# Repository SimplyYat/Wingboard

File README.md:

# Wingboard

> [!IMPORTANT]
> This is a work in progress.

A unibody ergonomic keyboard developed using [Ergogen](https://github.com/ergogen/ergogen) based on the [Absolem keyboard design](https://zealot.hu/absolem/).

## Row Column Matrix

## Components needed

Component | Type (THT, SMD, or No Solder) | Link | Quantity | LCSC Part Number (for SMT Assembly through JLCPCB)
---------|---------|----------|---------|---------
 Diode SOD-123/323 (1N4148/W) | SMD | [AliExpress](https://www.aliexpress.com/item/1005003194674618.html?spm=a2g0o.productlist.main.1.573bJia8Jia8Wb&algo_pvid=a8ea4330-8dd0-4ccf-9e2d-acbd802ee4b5&algo_exp_id=a8ea4330-8dd0-4ccf-9e2d-acbd802ee4b5-0&pdp_npi=4%40dis%21AUD%210.59%210.59%21%21%210.36%210.36%21%402103277f17365036595674485e2399%2112000024602962919%21sea%21AU%214011953287%21X&curPageLogUid=sZfdotSVyEA4&utparam-url=scene%3Asearch%7Cquery_from%3A) | 48 | [C81598](https://jlcpcb.com/partdetail/st_semtech-1N4148W/C81598)
 Kailh Low Profile Hot Swap Switches | SMD | [AliExpress](https://www.aliexpress.com/item/1005003575767699.html?spm=a2g0o.detail.0.0.52b8WBreWBreoo&mp=1) | 48 | [C5333465](https://jlcpcb.com/partdetail/Kailh-CPG135001S30/C5333465)
 Choc V2 Key Switches | No Solder | [Deep Sea Silent Switches](https://www.aliexpress.com/item/1005008113631450.html?spm=a2g0o.detail.0.0.52b8WBreWBreoo&mp=1), [Choose from here](https://www.aliexpress.com/item/1005006626760418.html?spm=a2g0o.detail.0.0.52b8WBreWBreoo&mp=1), or find your own | 48 | Manual install
 Choc V2 Key Caps | No Solder | 48 | Manual install
 Supermini NRF52840 MCU | THT | [AliExpress](https://www.aliexpress.com/item/1005001621678794.html?spm=a2g0o.productlist.main.3.22256MXM6MXMOc&algo_pvid=cc1cb5f0-bcd5-4dfa-9185-add9e4eee768&algo_exp_id=cc1cb5f0-bcd5-4dfa-9185-add9e4eee768-1&pdp_npi=4%40dis%21AUD%215.83%215.83%21%21%213.56%213.56%21%402101c5b217365044374885419ea55b%2112000016846541261%21sea%21AU%214011953287%21X&curPageLogUid=yQVmE2QrahaR&utparam-url=scene%3Asearch%7Cquery_from%3A) | 1 | Manual install
 Nice!View Display | THT | [Nice!View](https://nicekeyboards.com/nice-view) | 1 | Manual install
 EC11/12 Rotary Encoder | THT | [AliExpress](https://www.aliexpress.com/item/1005007644083514.html?spm=a2g0o.productlist.main.13.5ebdEX6cEX6cZx&algo_pvid=fe1462be-7885-4ea1-ad0e-55a54c8f8da5&algo_exp_id=fe1462be-7885-4ea1-ad0e-55a54c8f8da5-6&pdp_npi=4%40dis%21AUD%214.01%214.01%21%21%212.45%212.45%21%402101c5bf17366540947572842efcf2%2112000041630839429%21sea%21AU%214011953287%21X&curPageLogUid=Nk5ZhleEhhVZ&utparam-url=scene%3Asearch%7Cquery_from%3A) | 1 | Manual install
 Knob for the rotary encoder shaft | No Solder | [AliExpress](https://www.aliexpress.com/item/1005004171280417.html?spm=a2g0o.detail.0.0.52b8WBreWBreoo&mp=1) | 1 | Manual install
 Side Push Reset Switch (EVQPUC02K) | SMD | [AliExpress](https://www.aliexpress.com/item/1005002845025014.html?spm=a2g0o.productlist.main.17.18d7uC3JuC3JYF&algo_pvid=e749117c-627b-4f83-b282-9ee8ecd8f51a&algo_exp_id=e749117c-627b-4f83-b282-9ee8ecd8f51a-8&pdp_npi=4%40dis%21AUD%212.60%212.60%21%21%2111.65%2111.65%21%402101c59817365046938023702e595e%2112000029951120592%21sea%21AU%214011953287%21X&curPageLogUid=ygLyKat249IV&utparam-url=scene%3Asearch%7Cquery_from%3A) | 1 | [C79174](https://jlcpcb.com/partdetail/Panasonic-EVQPUC02K/C79174)
 Power Switch | SMD | TBD | 1 | Manual install
 JST PH 2.0mm 2-Pin Connector for Battery | SMD | [AliExpress (Horizontal ones)](https://www.aliexpress.com/item/1005005716487667.html?spm=a2g0o.productlist.main.5.67c455a9adJlS7&algo_pvid=41dd92c8-d88c-4ea2-bfcc-14092ce2489a&algo_exp_id=41dd92c8-d88c-4ea2-bfcc-14092ce2489a-2&pdp_npi=4%40dis%21AUD%214.11%213.21%21%21%212.51%211.96%21%402103247017365042545152094e1659%2112000034101497981%21sea%21AU%214011953287%21X&curPageLogUid=cfPpyCUyls7w&utparam-url=scene%3Asearch%7Cquery_from%3A) | 1 | [C7527581](https://jlcpcb.com/partdetail/Lian_XinTechnology-XDWF_092002P/C7527581)

## How to build
1. Order the PCB from the `pcb/production` folder through your preferred PCB fabrication service like JLCPCB, PCBWay, etc.
2. If you're ordering through JLCPCB, you can optionally use their SMT Assembly service to solder some components for you, the LCSC parts number are already added to the PCB, use the `pcb/production/bom.csv` and `pcb/production/positions.csv` as the BOM and Pick and Place files, respectively. Currently, the PCB includes LCSC part numbers for the bottom side only, for these parts (check the LCSC column above for links):
   1. 1N4148W SMD Diodes
   2. Kailh Low Profile Hot Swap Switches (they didn't have these in stock, so I couldn't order them, but they're there for when they have stock)
   3. Side Push Reset Switch (EVQPUC02K)
   4. JST PH 2.0mm 2-Pin Connector for Battery
   5. SMD Slider Power Switch
3. Source the rest of the components from your preferred suppliers and get to Soldering.
4. I'm still working on building a top case for this keyboard, so stay tuned for updates.

## Pending Items
1. [ ] Add top case with cutouts for:
    1. [ ] Nice view display
    2. [ ] Reset switch (TL3342 low profile - 2mm+ hole at the top)
    3. [ ] EC11/12 rotary encoder
    4. [ ] Power switch
    5. [ ] USB-C port
    6. [ ] Screw holes
 2. [ ] Adjust bottom case height to allow battery and PCB clearance
 3. [x] Route PCB
 4. [x] Add Wings image to PCB (Nice to have) 

## Notes
1. To get this repo, including the submodule `kb_ergogen_helper`, run the following command:
```bash
git clone --recursive <URL of this repo>
```
2. Since the addition of the `Makefile`, the following command can be used to build the output, convert the *.jscad* files to *.stl* in the `output/cases` path, and update traces on the PCB from last changes:
```bash
make build
```
3. If the make command above doesn't work, then build the output and convert the *.jscad* files to *.stl* in the `output/cases` path, run the following command from the current directory:
```bash
ergogen . && for f in output/cases/*.jscad; do npx @jscad/cli@1 $f -of stla -o ${f%.*}.stl; done
```
OR
```powershell
foreach ($file in Get-Item .\output\cases\*.jscad) {
   $basefilename=[System.IO.Path]::GetFileNameWithoutExtension($file.Name)
   npx @jscad/cli@1 $file -of stla -o ./output/cases/$basefilename.stl
}
```

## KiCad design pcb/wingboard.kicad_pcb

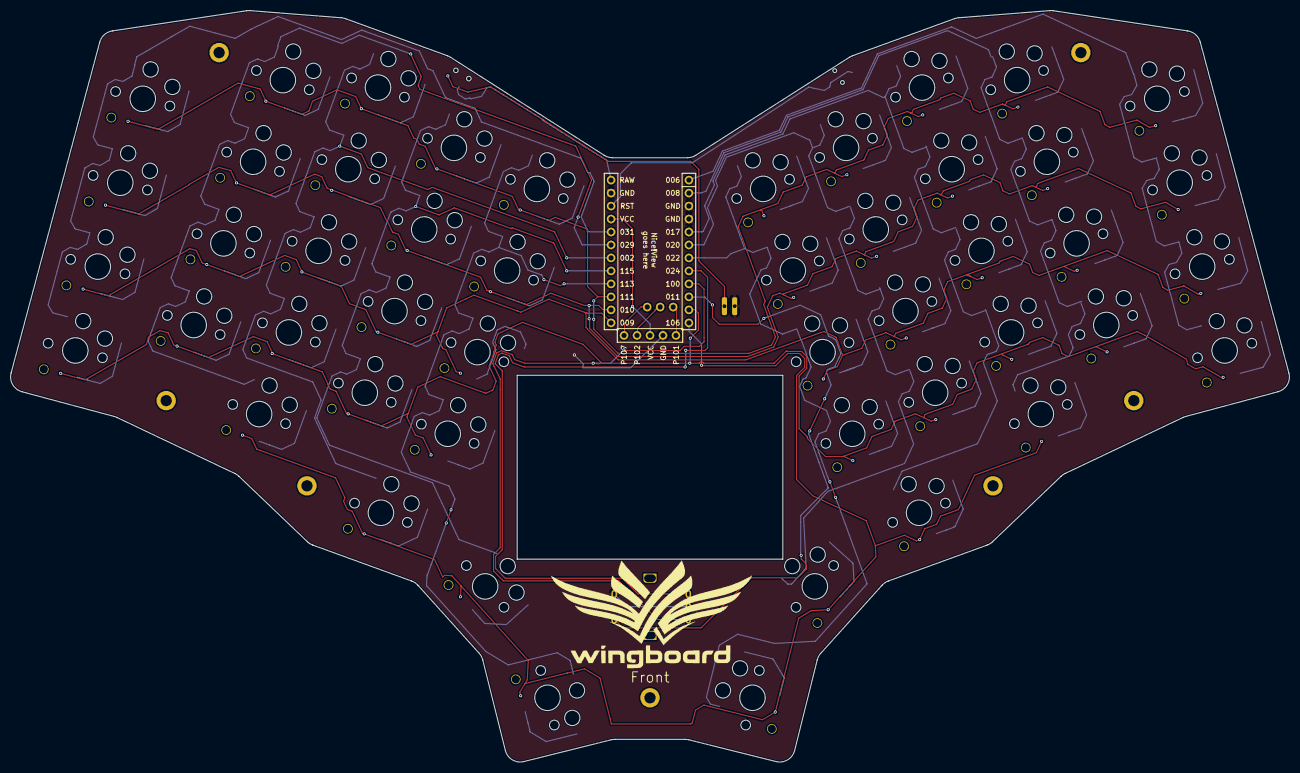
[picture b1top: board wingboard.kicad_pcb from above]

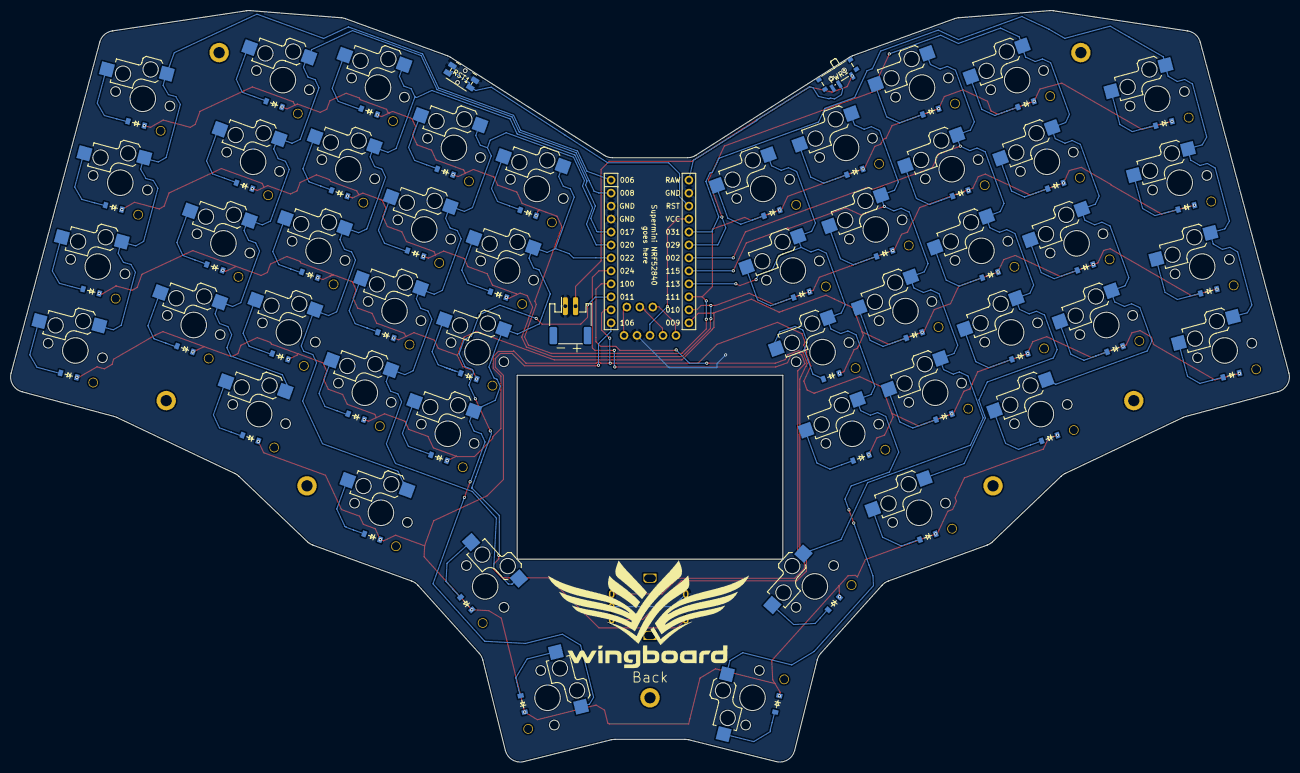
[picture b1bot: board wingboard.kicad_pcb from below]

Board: 2 copper layers, 250.3 x 147.1 mm, 109 parts (99 on the bottom side), 74 nets.

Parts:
D1, D2, D3, D4, D5, D6, D7, D8, D9, D10, D11, D12, D13, D14, D15, D16, D17, D18, D19, D20, D21, D22, D23, D24, D25, D26, D27, D28, D29, D30, D31, D32, D33, D34, D35, D36, D37, D38, D39, D40, D41, D42, D43, D44, D45, D46, D47, D48: diode_tht_sod123
DISP1: display_nice_view
H1, H2, H3, H4, H5, H6, H7: mounting_hole_plated
JST_BAT1: JST_PH_S2B-PH-SM4-TB_1x02-1MP_P2.00mm_Horizontal
MCU1: mcu_supermini_nrf52840
PWR1: SW_SPDT_PCM12
RE1: rotary_encoder_ec11_ec12
RST1: Panasonic_EVQPUL_EVQPUC
S1, S2, S3, S4, S5, S6, S7, S8, S9, S10, S11, S12, S13, S14, S15, S16, S17, S18, S19, S20, S21, S22, S23, S24, S25, S26, S27, S28, S29, S30, S31, S32, S33, S34, S35, S36, S37, S38, S39, S40, S41, S42, S43, S44, S45, S46, S47, S48: switch_choc_v1_v2

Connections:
BAT_P: JST_BAT1.2, PWR1.1
GND: DISP1.4, JST_BAT1.1, MCU1.3, MCU1.4, MCU1.23, RE1.B, RE1.S2, RST1.1
P002: MCU1.18, S10.1, S11.1, S12.1, S13.1, S22.1
P006: MCU1.1, S25.1, S26.1, S27.1, S28.1
P008: MCU1.2, S29.1, S30.1, S31.1, S32.1, S33.1
P009: D2.1, D6.1, D11.1, D15.1, D19.1, D26.1, D30.1, D35.1, D39.1, D43.1, MCU1.13
P010: D3.1, D7.1, D12.1, D16.1, D20.1, D27.1, D31.1, D36.1, D40.1, D44.1, MCU1.14
P011: MCU1.10, RE1.S1
P017: MCU1.5, S34.1, S35.1, S36.1, S37.1, S46.1
P020: MCU1.6, S38.1, S39.1, S40.1, S41.1, S47.1
P022: MCU1.7, S42.1, S43.1, S44.1, S45.1, S48.1
P024: MCU1.8, RE1.A
P029: MCU1.19, S5.1, S6.1, S7.1, S8.1, S9.1
P031: MCU1.20, S1.1, S2.1, S3.1, S4.1
P100: MCU1.9, RE1.C
P101: DISP1.5, MCU1.25
P102: DISP1.2, MCU1.26
P104: D1.1, D5.1, D10.1, D14.1, D18.1, D25.1, D29.1, D34.1, D38.1, D42.1, MCU1.11
P106: D9.1, D22.1, D23.1, D24.1, D33.1, D46.1, D47.1, D48.1, MCU1.12
P107: DISP1.1, MCU1.27
P111: D4.1, D8.1, D13.1, D17.1, D21.1, D28.1, D32.1, D37.1, D41.1, D45.1, MCU1.15
P113: MCU1.16, S18.1, S19.1, S20.1, S21.1, S24.1
P115: MCU1.17, S14.1, S15.1, S16.1, S17.1, S23.1
RAW: MCU1.24, PWR1.2
RST: MCU1.22, RST1.2
VCC: DISP1.3, MCU1.21
far_thumb: D24.2, S24.2
home_thumb: D23.2, S23.2
index_r1: D17.2, S17.2
index_r2: D16.2, S16.2
index_r3: D15.2, S15.2
index_r4: D14.2, S14.2
inner_r1: D21.2, S21.2
inner_r2: D20.2, S20.2
inner_r3: D19.2, S19.2
inner_r4: D18.2, S18.2
middle_r1: D13.2, S13.2
middle_r2: D12.2, S12.2
middle_r3: D11.2, S11.2
middle_r4: D10.2, S10.2
middle_r5: D9.2, S9.2
mirror_far_thumb: D48.2, S48.2
mirror_home_thumb: D47.2, S47.2
mirror_index_r1: D41.2, S41.2
mirror_index_r2: D40.2, S40.2
mirror_index_r3: D39.2, S39.2
mirror_index_r4: D38.2, S38.2
mirror_inner_r1: D45.2, S45.2
mirror_inner_r2: D44.2, S44.2
mirror_inner_r3: D43.2, S43.2
mirror_inner_r4: D42.2, S42.2
mirror_middle_r1: D37.2, S37.2
mirror_middle_r2: D36.2, S36.2
mirror_middle_r3: D35.2, S35.2
mirror_middle_r4: D34.2, S34.2
mirror_middle_r5: D33.2, S33.2
mirror_near_thumb: D46.2, S46.2
mirror_pinky_r1: D28.2, S28.2
mirror_pinky_r2: D27.2, S27.2
mirror_pinky_r3: D26.2, S26.2
mirror_pinky_r4: D25.2, S25.2
mirror_ring_r1: D32.2, S32.2
mirror_ring_r2: D31.2, S31.2
mirror_ring_r3: D30.2, S30.2
mirror_ring_r4: D29.2, S29.2
near_thumb: D22.2, S22.2
pinky_r1: D4.2, S4.2
pinky_r2: D3.2, S3.2
pinky_r3: D2.2, S2.2
pinky_r4: D1.2, S1.2
ring_r1: D8.2, S8.2
ring_r2: D7.2, S7.2
ring_r3: D6.2, S6.2
ring_r4: D5.2, S5.2

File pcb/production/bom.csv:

Designator,Footprint,Quantity,Value,LCSC Part #
"D1, D10, D11, D12, D13, D14, D15, D16, D17, D18, D19, D2, D20, D21, D22, D23, D24, D25, D26, D27, D28, D29, D3, D30, D31, D32, D33, D34, D35, D36, D37, D38, D39, D4, D40, D41, D42, D43, D44, D45, D46, D47, D48, D5, D6, D7, D8, D9",diode_tht_sod123,48,,C81598
"H1, H2, H3, H4, H5, H6, H7",mounting_hole_plated,7,,
JST_BAT1,JST_PH_S2B-PH-SM4-TB_1x02-1MP_P2.00mm_Horizontal,1,JST_PH_S2B-PH-SM4-TB_1x02-1MP_P2.00mm_Horizontal,C7527581
PWR1,SW_SPDT_PCM12,1,SW_SPDT_PCM12,C128955
RE1,rotary_encoder_ec11_ec12,1,,
RST1,Panasonic_EVQPUL_EVQPUC,1,Panasonic_EVQPUL_EVQPUC,C79174
"S1, S10, S11, S12, S13, S14, S15, S16, S17, S18, S19, S2, S20, S21, S22, S23, S24, S25, S26, S27, S28, S29, S3, S30, S31, S32, S33, S34, S35, S36, S37, S38, S39, S4, S40, S41, S42, S43, S44, S45, S46, S47, S48, S5, S6, S7, S8, S9",switch_choc_v1_v2,48,,C5333465

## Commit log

2025-01-04 Added Readme
2025-01-04 Updated row column matrix connections
2025-01-04 Added mounting holes and case
2025-01-04 Added mounting holes and cases
2025-01-04 Updated readme and config
2025-01-04 Create LICENSE
2025-01-05 Replaced choc with choc v2 footprints and updated readme
2025-01-05 Added cutouts for top plate for nice view and reset button
2025-01-05 Reorder stuff
2025-01-05 Replaced top reset switch with side switch and added submodule ergogen helper
2025-01-05 Added Makefile to copy Kicad traces using kb_ergogen_helper
2025-01-05 Added cutout for rotary encoder
2025-01-06 Added Makefile and pcb folder
2025-01-06 Added make command to readme
2025-01-06 Updated pcb
2025-01-07 Updated config to change column connections
2025-01-07 More PCB routing changes
2025-01-08 PCB routing and added S1 and S2 connections for Rotary Encoder
2025-01-08 Fixed makefile
2025-01-08 Updated the PCB
2025-01-09 Updated PCB and config
2025-01-10 Updated PCB, added new image footprint, and updated config
2025-01-10 New image footprint
2025-01-11 Added new footprints, updated PCB and config
2025-01-11 Updated footprints and config
2025-01-11 Added battery connector footprint
2025-01-12 Created Production PCB and updated Readme
2025-01-20 Updated config
2025-01-24 Added mocked assembled PCB
2025-01-24 Adding nice view assembly on pcb
2025-01-26 Update config and added ZMK firmware to use
2025-01-27 Updated config and decided to make stuff happen in Fusion instead of mocking everything in ergogen
